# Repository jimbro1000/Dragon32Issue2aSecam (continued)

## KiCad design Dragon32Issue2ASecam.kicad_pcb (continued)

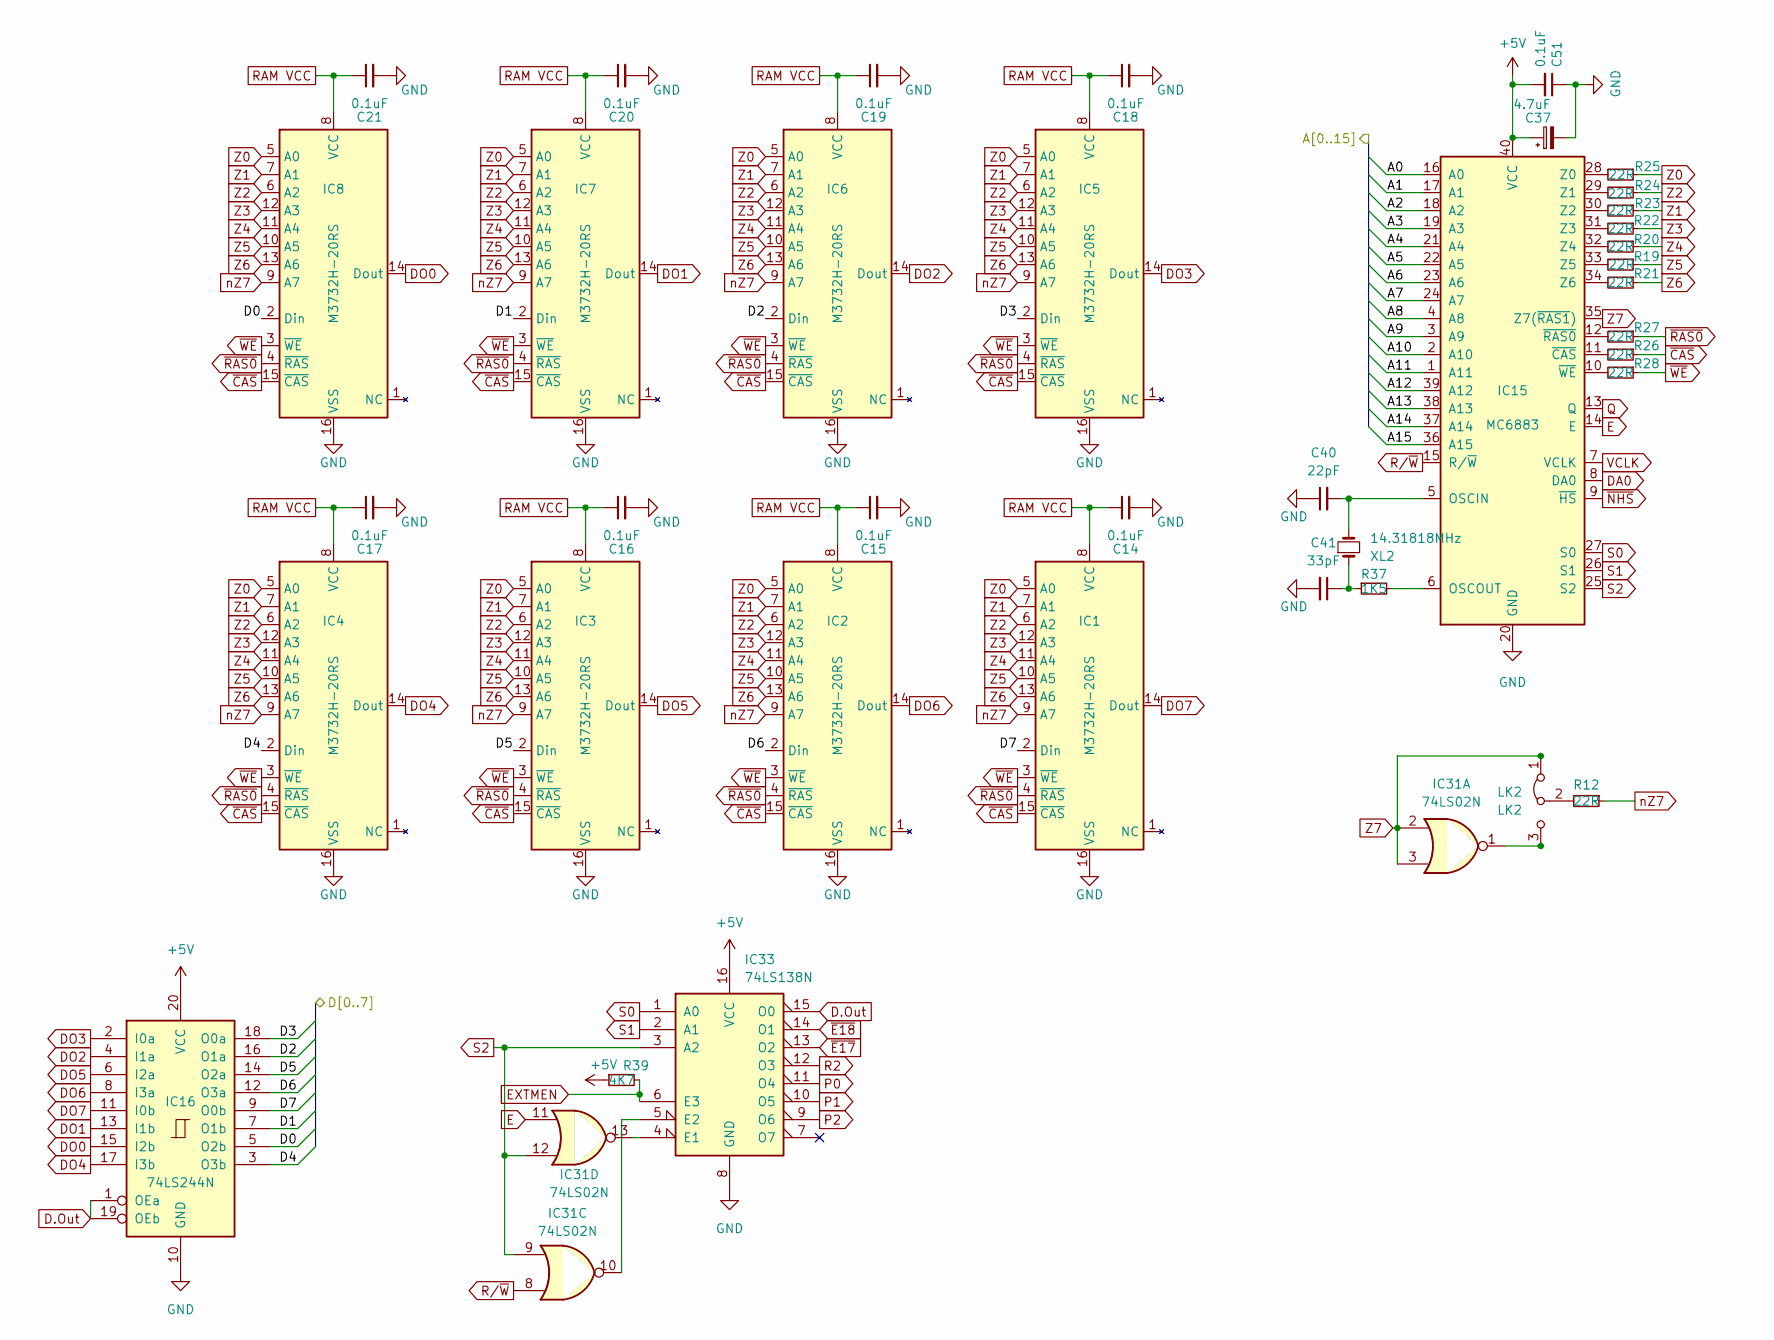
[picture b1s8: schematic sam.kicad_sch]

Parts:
C14, C15, C16, C17, C18, C19, C20, C21, C51: 0.1uF; C_Disc_D4.3mm_W1.9mm_P5.00mm; DigiKey BC1101CT-ND
C37: 4.7uF; CP_Radial_Tantal_D5.5mm_P5.00mm; DigiKey 478-8984-1-ND
C40: 22pF; C_Radial_Special; DigiKey 399-13930-1-ND
C41: 33pF; C_Disc_D3.0mm_W1.6mm_P2.50mm; DigiKey BC1007CT-ND
IC1, IC2, IC3, IC4, IC5, IC6, IC7, IC8: M3732H-20RS; DIP-16_W7.62mm
IC15: MC6883; DIP-40_W15.24mm
IC16: 74LS244N; DIP-20_W7.62mm; DigiKey 296-1653-5-ND
IC31: 74LS02N; DIP-14_W7.62mm; DigiKey 296-1627-5-ND
IC33: 74LS138N; DIP-16_W7.62mm; DigiKey 296-1639-5-ND
LK2: LK2; PinHeader_1x03_P2.54mm_Vertical; DigiKey 952-2521-ND
R12, R19, R20, R21, R22, R23, R24, R25, R26, R27, R28: 22R; R_Axial_DIN0309_L9.0mm_D2.5mm_P12.70mm_Horizontal; DigiKey CF14JT22R0CT-ND
R37: 1K5; R_Axial_DIN0309_L9.0mm_D2.5mm_P12.70mm_Horizontal; DigiKey CF14JT1K50CT-ND
R39: 4K7; R_Axial_DIN0309_L9.0mm_D2.5mm_P12.70mm_Horizontal; DigiKey CF14JT4K70CT-ND
XL2: 14.31818MHz; Crystal_HC49-U_Horizontal; DigiKey CTX088-ND

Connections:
+5V: C37.1, C51.2, IC15.40 (VCC), IC16.20 (VCC), IC33.16 (VCC), R39.1; also elsewhere on the board
/CPU/A0: IC15.16 (A0); also elsewhere on the board
/CPU/A1: IC15.17 (A1); also elsewhere on the board
/CPU/A2: IC15.18 (A2); also elsewhere on the board
/CPU/A3: IC15.19 (A3); also elsewhere on the board
/CPU/A4: IC15.21 (A4); also elsewhere on the board
/CPU/A5: IC15.22 (A5); also elsewhere on the board
/CPU/A6: IC15.23 (A6); also elsewhere on the board
/CPU/A7: IC15.24 (A7); also elsewhere on the board
/CPU/A8: IC15.4 (A8); also elsewhere on the board
/CPU/A9: IC15.3 (A9); also elsewhere on the board
/CPU/A10: IC15.2 (A10); also elsewhere on the board
/CPU/A11: IC15.1 (A11); also elsewhere on the board
/CPU/A12: IC15.39 (A12); also elsewhere on the board
/CPU/A13: IC15.38 (A13); also elsewhere on the board
/CPU/A14: IC15.37 (A14); also elsewhere on the board
/CPU/A15: IC15.36 (A15); also elsewhere on the board
/CPU/D0: IC8.2 (Din), IC16.5 (O2b); also elsewhere on the board
/CPU/D1: IC7.2 (Din), IC16.7 (O1b); also elsewhere on the board
/CPU/D2: IC6.2 (Din), IC16.16 (O1a); also elsewhere on the board
/CPU/D3: IC5.2 (Din), IC16.18 (O0a); also elsewhere on the board
/CPU/D4: IC4.2 (Din), IC16.3 (O3b); also elsewhere on the board
/CPU/D5: IC3.2 (Din), IC16.14 (O2a); also elsewhere on the board
/CPU/D6: IC2.2 (Din), IC16.12 (O3a); also elsewhere on the board
/CPU/D7: IC1.2 (Din), IC16.9 (O0b); also elsewhere on the board
D.Out: IC16.1 (OEa), IC16.19 (OEb), IC33.15 (O0)
DA0: IC15.8 (DA0); also elsewhere on the board
DO0: IC8.14 (Dout), IC16.15 (I2b); also elsewhere on the board
DO1: IC7.14 (Dout), IC16.13 (I1b); also elsewhere on the board
DO2: IC6.14 (Dout), IC16.4 (I1a); also elsewhere on the board
DO3: IC5.14 (Dout), IC16.2 (I0a); also elsewhere on the board
DO4: IC4.14 (Dout), IC16.17 (I3b); also elsewhere on the board
DO5: IC3.14 (Dout), IC16.6 (I2a); also elsewhere on the board
DO6: IC2.14 (Dout), IC16.8 (I3a); also elsewhere on the board
DO7: IC1.14 (Dout), IC16.11 (I0b); also elsewhere on the board
E: IC15.14 (E), IC31.11; also elsewhere on the board
EXTMEN: IC33.6 (E3), R39.2; also elsewhere on the board
GND: C14.2, C15.2, C16.2, C17.2, C18.2, C19.2, C20.2, C21.2, C37.2, C40.1, C41.2, C51.1, IC1.16 (VSS), IC2.16 (VSS), IC3.16 (VSS), IC4.16 (VSS), IC5.16 (VSS), IC6.16 (VSS), IC7.16 (VSS), IC8.16 (VSS), IC15.20 (GND), IC16.10 (GND), IC33.8 (GND); also elsewhere on the board
unnamed: C41.1, R37.1, XL2.1
unnamed: C40.2, IC15.5 (OSCIN), XL2.2
unnamed: IC15.6 (OSCOUT), R37.2
unnamed: IC15.28 (Z0), R25.2
unnamed: IC15.29 (Z1), R24.2
unnamed: IC15.30 (Z2), R23.2
unnamed: IC15.31 (Z3), R22.2
unnamed: IC15.32 (Z4), R20.2
unnamed: IC15.33 (Z5), R19.2
unnamed: IC15.34 (Z6), R21.2
unnamed: IC15.11 (~CAS), R26.2
unnamed: IC15.12 (~RAS0), R27.2
unnamed: IC15.10 (~WE), R28.2
unnamed: IC31.13, IC33.4 (E1)
unnamed: IC31.10, IC33.5 (E2)
unnamed: IC31.1, LK2.3 (B)
P0: IC33.11 (O4); also elsewhere on the board
P1: IC33.10 (O5); also elsewhere on the board
P2: IC33.9 (O6); also elsewhere on the board
Q: IC15.13 (Q); also elsewhere on the board
R2: IC33.12 (O3); also elsewhere on the board
RAM VCC: C14.1, C15.1, C16.1, C17.1, C18.1, C19.1, C20.1, C21.1, IC1.8 (VCC), IC2.8 (VCC), IC3.8 (VCC), IC4.8 (VCC), IC5.8 (VCC), IC6.8 (VCC), IC7.8 (VCC), IC8.8 (VCC)
R/~W: IC15.15 (R/~W), IC31.8; also elsewhere on the board
S0: IC15.27 (S0), IC33.1 (A0)
S1: IC15.26 (S1), IC33.2 (A1)
S2: IC15.25 (S2), IC31.9, IC31.12, IC33.3 (A2)
VCLK: IC15.7 (VCLK); also elsewhere on the board
Z0: IC1.5 (A0), IC2.5 (A0), IC3.5 (A0), IC4.5 (A0), IC5.5 (A0), IC6.5 (A0), IC7.5 (A0), IC8.5 (A0), R25.1
Z1: IC1.7 (A1), IC2.7 (A1), IC3.7 (A1), IC4.7 (A1), IC5.7 (A1), IC6.7 (A1), IC7.7 (A1), IC8.7 (A1), R23.1
Z2: IC1.6 (A2), IC2.6 (A2), IC3.6 (A2), IC4.6 (A2), IC5.6 (A2), IC6.6 (A2), IC7.6 (A2), IC8.6 (A2), R24.1
Z3: IC1.12 (A3), IC2.12 (A3), IC3.12 (A3), IC4.12 (A3), IC5.12 (A3), IC6.12 (A3), IC7.12 (A3), IC8.12 (A3), R22.1
Z4: IC1.11 (A4), IC2.11 (A4), IC3.11 (A4), IC4.11 (A4), IC5.11 (A4), IC6.11 (A4), IC7.11 (A4), IC8.11 (A4), R20.1
Z5: IC1.10 (A5), IC2.10 (A5), IC3.10 (A5), IC4.10 (A5), IC5.10 (A5), IC6.10 (A5), IC7.10 (A5), IC8.10 (A5), R19.1
Z6: IC1.13 (A6), IC2.13 (A6), IC3.13 (A6), IC4.13 (A6), IC5.13 (A6), IC6.13 (A6), IC7.13 (A6), IC8.13 (A6), R21.1
Z7: IC15.35 (Z7(~RAS1)), IC31.2, IC31.3, LK2.1 (A)
nZ7: IC1.9 (A7), IC2.9 (A7), IC3.9 (A7), IC4.9 (A7), IC5.9 (A7), IC6.9 (A7), IC7.9 (A7), IC8.9 (A7), R12.1
~CAS: IC1.15 (~CAS), IC2.15 (~CAS), IC3.15 (~CAS), IC4.15 (~CAS), IC5.15 (~CAS), IC6.15 (~CAS), IC7.15 (~CAS), IC8.15 (~CAS), R26.1
~E17: IC33.13 (O2); also elsewhere on the board
~E18: IC33.14 (O1); also elsewhere on the board
~NHS: IC15.9 (~HS); also elsewhere on the board
~RAS0: IC1.4 (~RAS), IC2.4 (~RAS), IC3.4 (~RAS), IC4.4 (~RAS), IC5.4 (~RAS), IC6.4 (~RAS), IC7.4 (~RAS), IC8.4 (~RAS), R27.1; also elsewhere on the board
~WE: IC1.3 (~WE), IC2.3 (~WE), IC3.3 (~WE), IC4.3 (~WE), IC5.3 (~WE), IC6.3 (~WE), IC7.3 (~WE), IC8.3 (~WE), R28.1

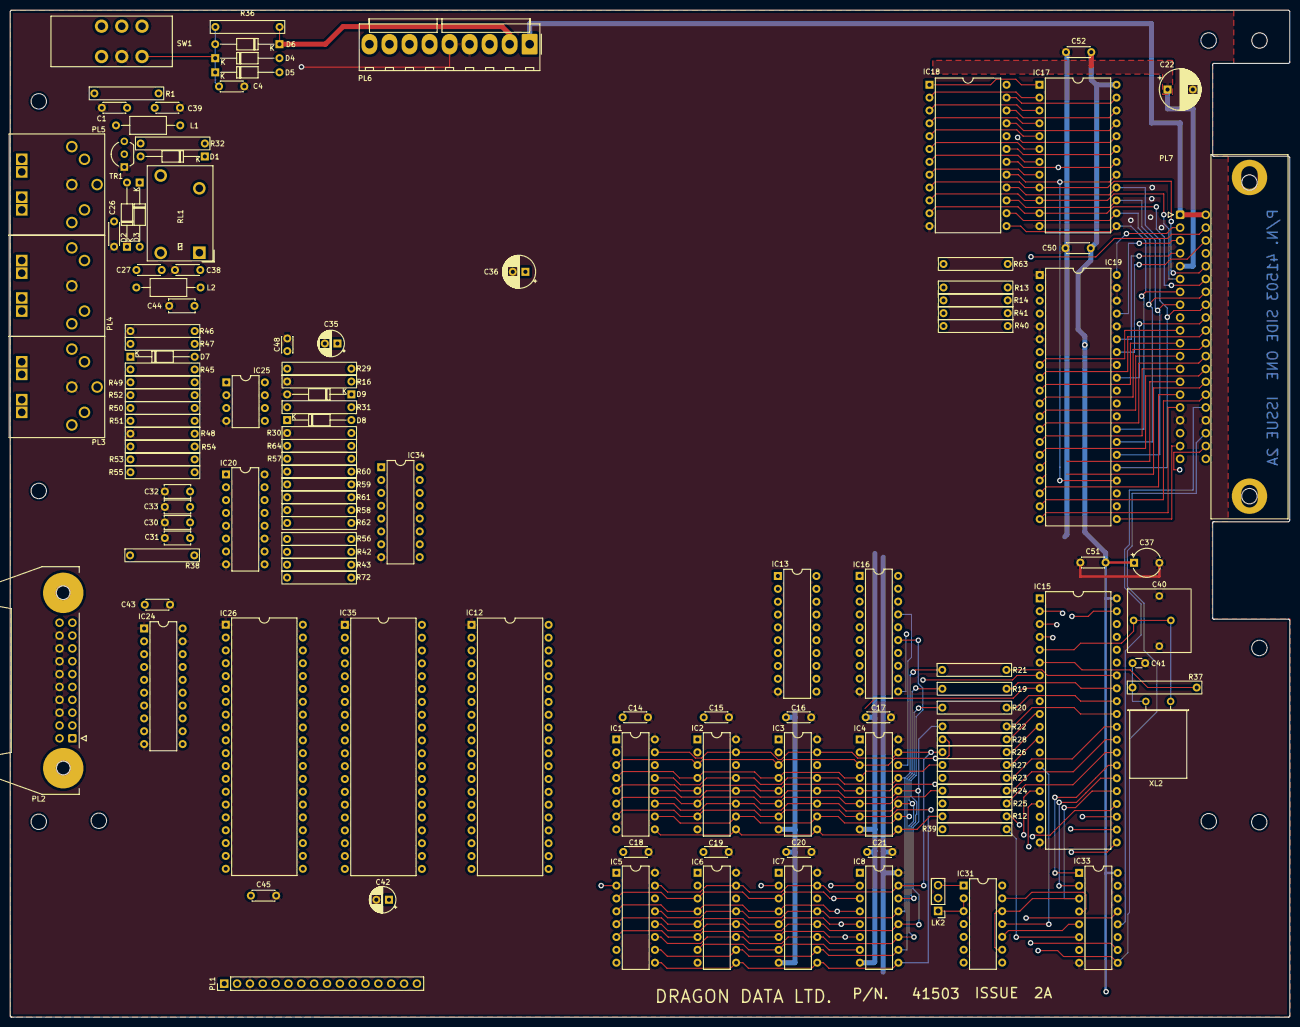
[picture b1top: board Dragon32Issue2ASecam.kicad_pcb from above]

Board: 2 copper layers, 252.9 x 199.0 mm, 126 parts (0 on the bottom side), 172 nets.

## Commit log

2025-01-27 add sam and ram
2025-01-28 work on memory sub system
2025-01-29 add PIA and VDG to schematics
2025-01-29 add video padding circuit
2025-01-29 update render
2025-01-31 video circuit tracing
2025-02-02 FM generator routing
2025-02-03 complete physical layout
2025-02-03 fm circuit routing
2025-02-03 trace work complete
2025-02-05 attach u5 to 4053-pin 15 (B control)
2025-02-11 resolve missing connections
2025-02-18 add missing power connections
